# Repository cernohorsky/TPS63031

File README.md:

# TPS63031 breakout board
High Efficiency Single Inductor Buck-Boost Converter With 1-A Switches

- Input Voltage Range: 1.8 V to 5.5 V
- Output Voltage 3.3 V up to 800 mA

http://www.ti.com/lit/ds/symlink/tps63030.pdf

<b>ToDo:</b><br>
DRC<br>

Idle current measurement (connected LoRa Node in sleep mode - 5 uA)

#TPS63031, #breakout, #buck-boost, #3v3, #battery

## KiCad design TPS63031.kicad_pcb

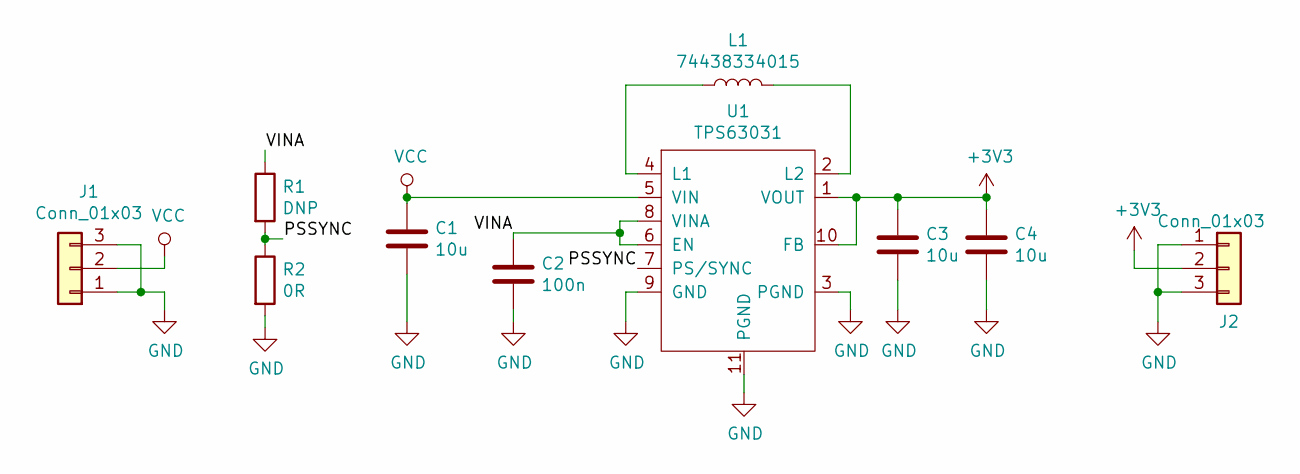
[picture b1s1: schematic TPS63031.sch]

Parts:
C1, C3, C4: 10u; C_0805_2012Metric
C2: 100n; C_0603_1608Metric
J1, J2: Conn_01x03; PinHeader_1x03_P2.54mm_Vertical
L1: 74438334015; L_Wuerth_MAPI-3012
R1: DNP; R_0603_1608Metric
R2: 0R; R_0603_1608Metric
U1: TPS63031; Texas_S-PWSON-N10

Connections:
+3V3: C3.1, C4.1, J2.2, U1.1 (VOUT), U1.10 (FB)
/PSSYNC: R1.2, R2.1, U1.7 (PS/SYNC)
/VINA: C2.1, R1.1, U1.6 (EN), U1.8 (VINA)
GND: C1.2, C2.2, C3.2, C4.2, J1.1, J1.3, J2.1, J2.3, R2.2, U1.3 (PGND), U1.9 (GND), U1.11 (PGND)
unnamed: L1.1, U1.4 (L1)
unnamed: L1.2, U1.2 (L2)
VCC: C1.1, J1.2, U1.5 (VIN)

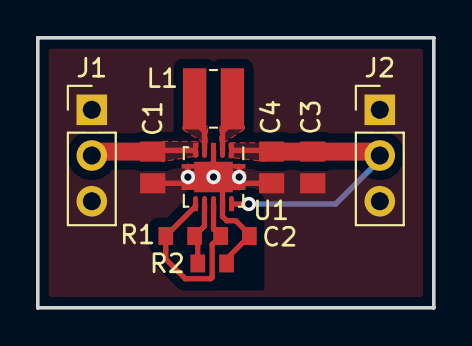
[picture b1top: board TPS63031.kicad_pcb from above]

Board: 2 copper layers, 22.0 x 15.0 mm, 10 parts (0 on the bottom side), 7 nets.

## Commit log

2019-03-18 v0.1
2019-03-22 Added lib file
2019-03-22 PCB manufactured
2019-05-10 Inductor type specification
2019-06-04 Added idle current measurement result
2019-06-06 Added description how to set converter mode
